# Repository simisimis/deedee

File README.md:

# DeeDee

A 36+2 key split monoblock ortholinear keyboard

## Current progress:

- [x] Key matrix
- [x] Layout defined
- [x] Addressable LEDs
- [x] Rotary encoders
- [ ] SSD1306 OLED screen
- [ ] Cirque touchpad
- [ ] Case design

A place where I try to document every step of the process is journalled in my [Project blog posts](https://github.com/simisimis/project-blog/tree/main/projects/DIY-keyboard) repo.

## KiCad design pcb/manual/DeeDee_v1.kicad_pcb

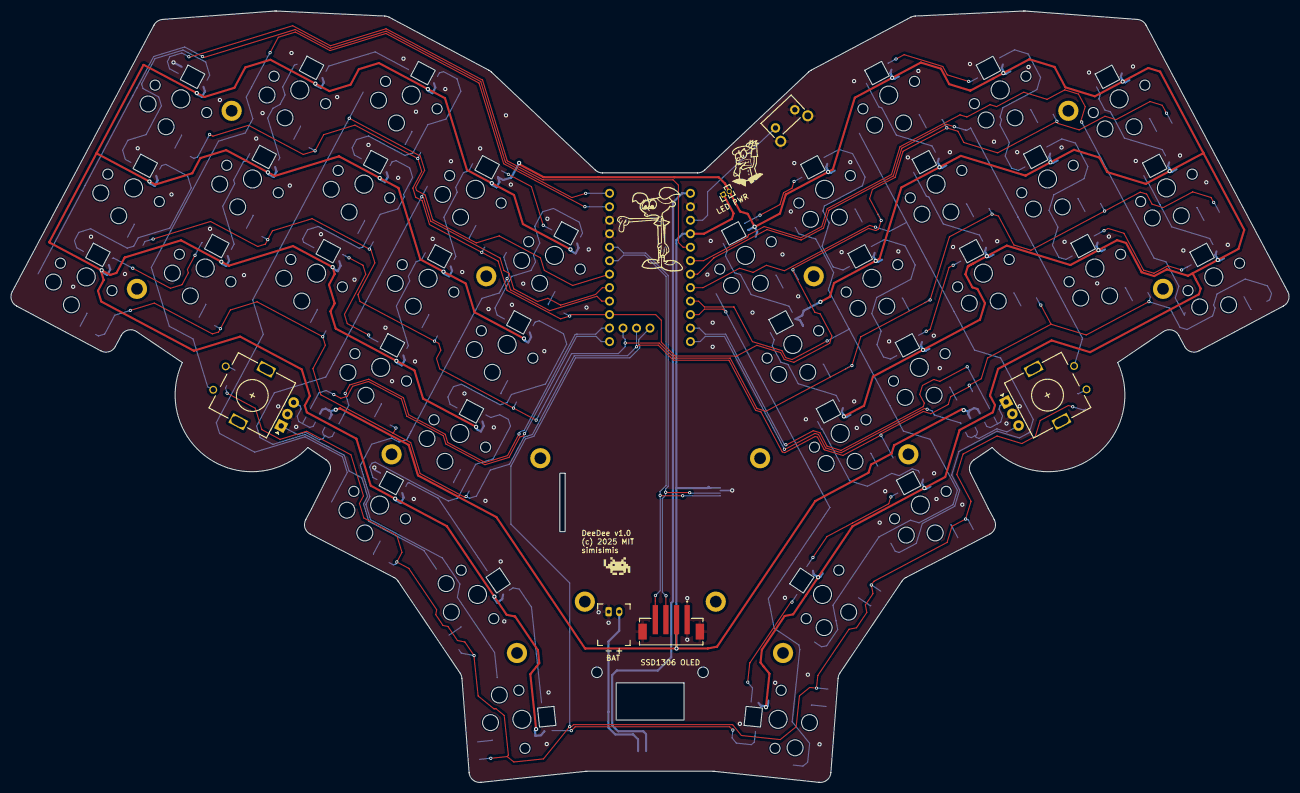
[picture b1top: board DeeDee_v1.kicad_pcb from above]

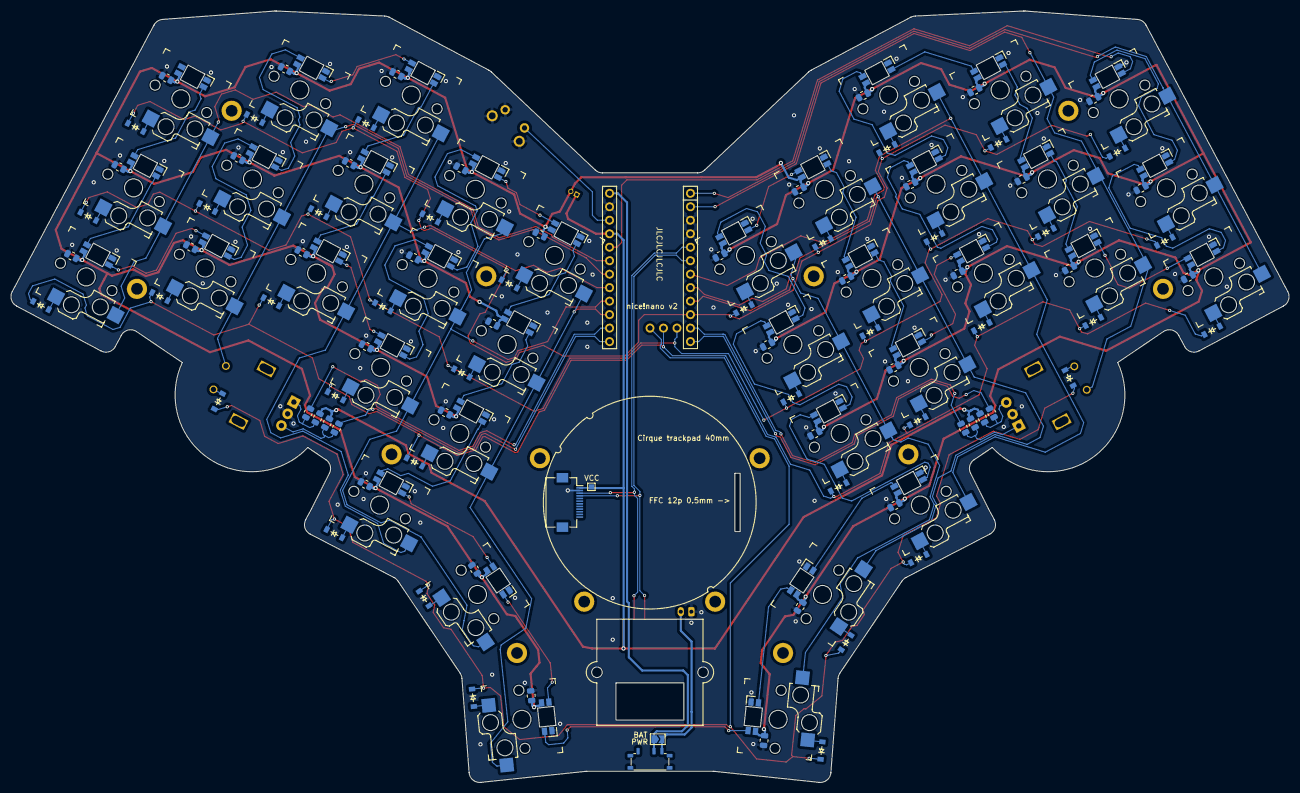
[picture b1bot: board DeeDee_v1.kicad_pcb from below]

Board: 2 copper layers, 240.8 x 145.3 mm, 169 parts (114 on the bottom side), 103 nets.

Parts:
BAT: battery_connector_jst_ph_2
BAT#2: SolderJumper-2_P1.3mm_Open_TrianglePad1.0x1.5mm
Cirque trackpad 40mm: FFC 12p 0.5mm; cirque_connector_12p_back
D1, D2, D3, D4, D5, D6, D7, D8, D9, D10, D11, D12, D13, D14, D15, D16, D17, D18, D19, D20, D21, D22, D23, D24, D25, D26, D27, D28, D29, D30, D31, D32, D33, D34, D35, D36, D37, D38: diode_tht_sod123
H1, H2, H3, H4, H5, H6, H7, H8, H8#2, H8#3, H9, H10: mounting_hole_plated
LED1, LED2, LED3, LED4, LED5, LED6, LED7, LED8, LED9, LED10, LED11, LED12, LED13, LED14, LED15, LED16, LED17, LED18, LED19, LED20, LED21, LED22, LED23, LED24, LED25, LED26, LED27, LED28, LED29, LED30, LED31, LED32, LED33, LED34, LED35, LED36: led_SK6812mini-e (per-keysingle-side)
LED PWR: PinHeader_1x02_P1.27mm_Vertical
MCU1: mcu_nice_nano
ROT1, ROT2: rotary_encoder
S1, S2, S3, S4, S5, S6, S7, S8, S9, S10, S11, S12, S13, S14, S15, S16, S17, S18, S19, S20, S21, S22, S23, S24, S25, S26, S27, S28, S29, S30, S31, S32, S33, S34, S35, S36: switch_choc_v1_v2
SMD1, SMD2, SMD3, SMD4, SMD5, SMD6, SMD7, SMD8, SMD9, SMD10, SMD11, SMD12, SMD13, SMD14, SMD15, SMD16, SMD17, SMD18, SMD19, SMD20, SMD21, SMD22, SMD23, SMD24, SMD25, SMD26, SMD27, SMD28, SMD29, SMD30, SMD31, SMD32, SMD33, SMD34, SMD35, SMD36, SMD37, SMD38: smd_805
SSD1306 OLED: SSD1306 OLED; jst-ph-smt-4p-2mm
VCC: TestPoint_Pad_1.0x1.0mm

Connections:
BAT_P: BAT.2, BAT#2.2
C1: MCU1.24, S1.2, S2.2, S3.2
C2: MCU1.23, ROT1.1, S4.2, S5.2, S6.2
C3: MCU1.18, S7.2, S8.2, S9.2, S31.2
C4: MCU1.17, S10.2, S11.2, S12.2, S32.2
C5: MCU1.16, S13.2, S14.2, S15.2, S33.2
C6: MCU1.10, S28.2, S29.2, S30.2, S36.2
C7: MCU1.9, S25.2, S26.2, S27.2, S35.2
C8: MCU1.8, S22.2, S23.2, S24.2, S34.2
C9: MCU1.7, ROT2.1, S19.2, S20.2, S21.2
C10: MCU1.6, S16.2, S17.2, S18.2
ELA: MCU1.14, SMD1.8
ELA_R: ROT1.A, SMD1.5, SMD1.7
ELB: MCU1.13, SMD1.2
ELB_R: ROT1.B, SMD1.1, SMD1.3
ERA: MCU1.11, SMD2.8
ERA_R: ROT2.A, SMD2.5, SMD2.7
ERB: MCU1.12, SMD2.2
ERB_R: ROT2.B, SMD2.1, SMD2.3
GND: BAT.1, Cirque trackpad 40mm.11, LED1.3, LED2.3, LED3.3, LED4.3, LED5.3, LED6.3, LED7.3, LED8.3, LED9.3, LED10.3, LED11.3, LED12.3, LED13.3, LED14.3, LED15.3, LED16.3, LED17.3, LED18.3, LED19.3, LED20.3, LED21.3, LED22.3, LED23.3, LED24.3, LED25.3, LED26.3, LED27.3, LED28.3, LED29.3, LED30.3, LED31.3, LED32.3, LED33.3, LED34.3, LED35.3, LED36.3, MCU1.2, MCU1.21, MCU1.22, ROT1.C, ROT2.C, SMD3.1, SMD4.1, SMD5.1, SMD6.1, SMD7.1, SMD8.1, SMD9.1, SMD10.1, SMD11.1, SMD12.1, SMD13.1, SMD14.1, SMD15.1, SMD16.1, SMD17.1, SMD18.1, SMD19.1, SMD20.1, SMD21.2, SMD22.2, SMD23.2, SMD24.2, SMD25.2, SMD26.2, SMD27.2, SMD28.2, SMD29.2, SMD30.2, SMD31.2, SMD32.2, SMD33.2, SMD34.2, SMD35.2, SMD36.2, SMD37.2, SMD38.2, SSD1306 OLED.1, SSD1306 OLED.SH1, SSD1306 OLED.SH2
LED: LED3.4, MCU1.5
LED_1: LED2.4, LED3.2
LED_2: LED1.4, LED2.2
LED_3: LED1.2, LED4.4
LED_4: LED4.2, LED5.4
LED_5: LED5.2, LED6.4
LED_6: LED6.2, LED9.4
LED_7: LED8.4, LED9.2
LED_8: LED7.4, LED8.2
LED_9: LED7.2, LED10.4
LED_10: LED10.2, LED11.4
LED_11: LED11.2, LED12.4
LED_12: LED12.2, LED15.4
LED_13: LED14.4, LED15.2
LED_14: LED13.4, LED14.2
LED_15: LED13.2, LED16.4
LED_16: LED16.2, LED17.4
LED_17: LED17.2, LED18.4
LED_18: LED18.2, LED36.4
LED_19: LED35.4, LED36.2
LED_20: LED34.4, LED35.2
LED_21: LED31.4, LED34.2
LED_22: LED31.2, LED32.4
LED_23: LED32.2, LED33.4
LED_24: LED30.4, LED33.2
LED_25: LED29.4, LED30.2
LED_26: LED28.4, LED29.2
LED_27: LED25.4, LED28.2
LED_28: LED25.2, LED26.4
LED_29: LED26.2, LED27.4
LED_30: LED24.4, LED27.2
LED_31: LED23.4, LED24.2
LED_32: LED22.4, LED23.2
LED_33: LED19.4, LED22.2
LED_34: LED19.2, LED20.4
LED_35: LED20.2, LED21.4
R1: D3.1, D6.1, D9.1, D12.1, D15.1, D22.1, D25.1, D28.1, D31.1, D34.1, MCU1.15
R2: D2.1, D5.1, D8.1, D11.1, D14.1, D21.1, D24.1, D27.1, D30.1, D33.1, MCU1.25
R3: D1.1, D4.1, D7.1, D10.1, D13.1, D20.1, D23.1, D26.1, D29.1, D32.1, MCU1.26
R4: D16.1, D17.1, D18.1, D19.1, D35.1, D36.1, D37.1, D38.1, MCU1.27
RAW: BAT#2.1, MCU1.1
SCL: Cirque trackpad 40mm.9, MCU1.19, SSD1306 OLED.4
SDA: Cirque trackpad 40mm.10, MCU1.20, SSD1306 OLED.3
VCC: Cirque trackpad 40mm.12, LED PWR.1, MCU1.4, SMD1.4, SMD1.6, SMD2.4, SMD2.6, SSD1306 OLED.2, VCC.1
VCC_LED: LED1.1, LED2.1, LED3.1, LED4.1, LED5.1, LED6.1, LED7.1, LED8.1, LED9.1, LED10.1, LED11.1, LED12.1, LED13.1, LED14.1, LED15.1, LED16.1, LED17.1, LED18.1, LED19.1, LED20.1, LED21.1, LED22.1, LED23.1, LED24.1, LED25.1, LED26.1, LED27.1, LED28.1, LED29.1, LED30.1, LED31.1, LED32.1, LED33.1, LED34.1, LED35.1, LED36.1, LED PWR.2, SMD3.2, SMD4.2, SMD5.2, SMD6.2, SMD7.2, SMD8.2, SMD9.2, SMD10.2, SMD11.2, SMD12.2, SMD13.2, SMD14.2, SMD15.2, SMD16.2, SMD17.2, SMD18.2, SMD19.2, SMD20.2, SMD21.1, SMD22.1, SMD23.1, SMD24.1, SMD25.1, SMD26.1, SMD27.1, SMD28.1, SMD29.1, SMD30.1, SMD31.1, SMD32.1, SMD33.1, SMD34.1, SMD35.1, SMD36.1, SMD37.1, SMD38.1
enc_enc: D19.2, ROT1.2
far_home: D18.2, S33.1
index_bottom: D10.2, S10.1
index_home: D11.2, S11.1
index_top: D12.2, S12.1
inner_bottom: D13.2, S13.1
inner_home: D14.2, S14.1
inner_top: D15.2, S15.1
mid_home: D17.2, S32.1
middle_bottom: D7.2, S7.1
middle_home: D8.2, S8.1
middle_top: D9.2, S9.1
mirror_enc_enc: D38.2, ROT2.2
mirror_far_home: D37.2, S36.1
mirror_index_bottom: D29.2, S25.1
mirror_index_home: D30.2, S26.1
mirror_index_top: D31.2, S27.1
mirror_inner_bottom: D32.2, S28.1
mirror_inner_home: D33.2, S29.1
mirror_inner_top: D34.2, S30.1
mirror_mid_home: D36.2, S35.1
mirror_middle_bottom: D26.2, S22.1
mirror_middle_home: D27.2, S23.1
mirror_middle_top: D28.2, S24.1
mirror_near_home: D35.2, S34.1
mirror_pinky_bottom: D20.2, S16.1
mirror_pinky_home: D21.2, S17.1
mirror_pinky_top: D22.2, S18.1
mirror_ring_bottom: D23.2, S19.1
mirror_ring_home: D24.2, S20.1
mirror_ring_top: D25.2, S21.1
near_home: D16.2, S31.1
pinky_bottom: D1.2, S1.1
pinky_home: D2.2, S2.1
pinky_top: D3.2, S3.1
ring_bottom: D4.2, S4.1
ring_home: D5.2, S5.1
ring_top: D6.2, S6.1

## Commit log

2024-04-09 nice nano blink
2024-04-16 reorganize
2024-04-23 checkpoint for board with keys/diodes/mcu/rotary
2024-06-02 save progress
2024-11-19 picking up after the break
2024-12-30 overdue commit of many parts
2025-01-30 rm backup file
2025-01-30 DeeDee v1 milestone
2025-02-05 add zmk init files
2025-02-05 actions change 1
2025-02-18 call local action adjust the paths Add zmk config for DeeDee Add DeeDee zmk conf enable logging for debugging fix row0 pin mapping try gpio1 instead of pro_micro to fix columns Fix screwholes. Add bo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
2025-02-18 add ec12 encoder configuration
2025-02-21 tune EC11,EC12 encoders
2025-02-21 update ceoloide footprints

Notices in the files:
pcb/manual/DeeDee_v1.kicad_pcb:
(c) 2025 MIT
